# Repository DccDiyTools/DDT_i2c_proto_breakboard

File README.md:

# DDT_i2c_proto_breakboard
Breakboard of the DDT_i2c_proto specs

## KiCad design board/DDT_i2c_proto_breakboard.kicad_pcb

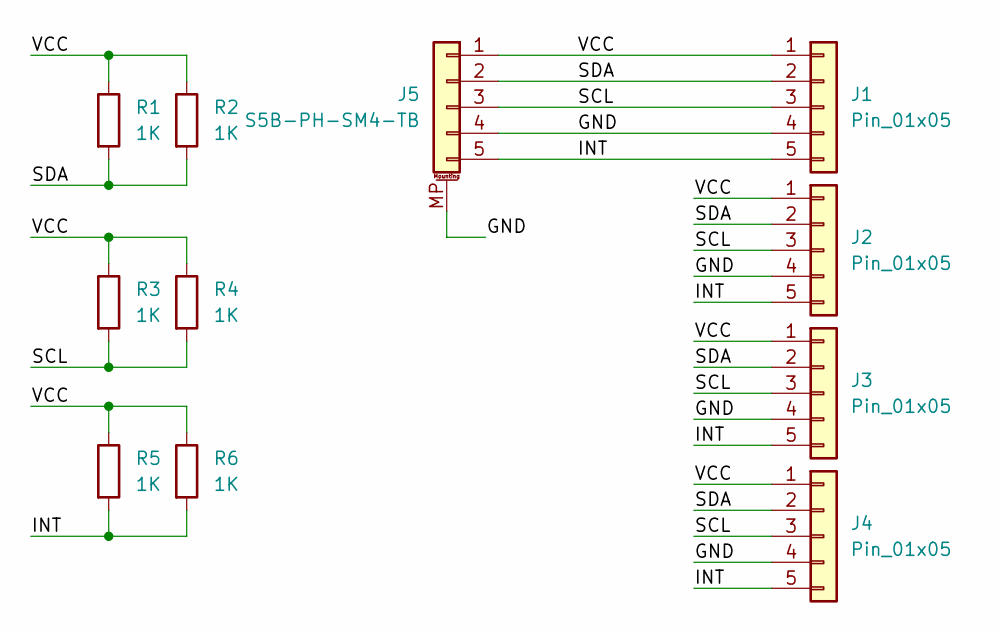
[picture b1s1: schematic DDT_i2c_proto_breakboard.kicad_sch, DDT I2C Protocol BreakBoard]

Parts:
J1, J2, J3, J4: Pin_01x05; PinHeader_1x05_P2.54mm_Vertical
J5: S5B-PH-SM4-TB; JST_PH_S5B-PH-SM4-TB_1x05-1MP_P2.00mm_Horizontal
R1, R3, R5: 1K; R_1206_3216Metric_Pad1.30x1.75mm_HandSolder
R2, R4, R6: 1K; R_Axial_DIN0309_L9.0mm_D3.2mm_P12.70mm_Horizontal

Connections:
/GND: J1.4, J2.4, J3.4, J4.4, J5.4, J5.MP (MountPin)
/INT: J1.5, J2.5, J3.5, J4.5, J5.5, R5.2, R6.2
/SCL: J1.3, J2.3, J3.3, J4.3, J5.3, R3.2, R4.2
/SDA: J1.2, J2.2, J3.2, J4.2, J5.2, R1.2, R2.2
/VCC: J1.1, J2.1, J3.1, J4.1, J5.1, R1.1, R2.1, R3.1, R4.1, R5.1, R6.1

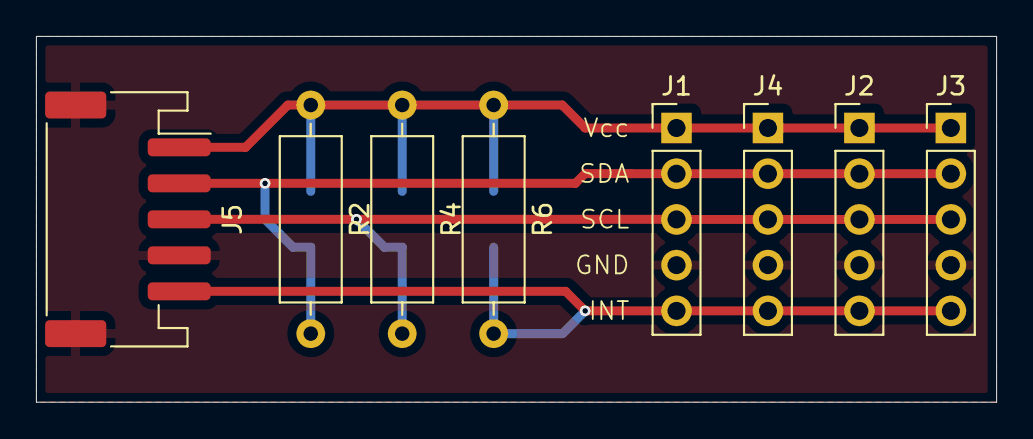
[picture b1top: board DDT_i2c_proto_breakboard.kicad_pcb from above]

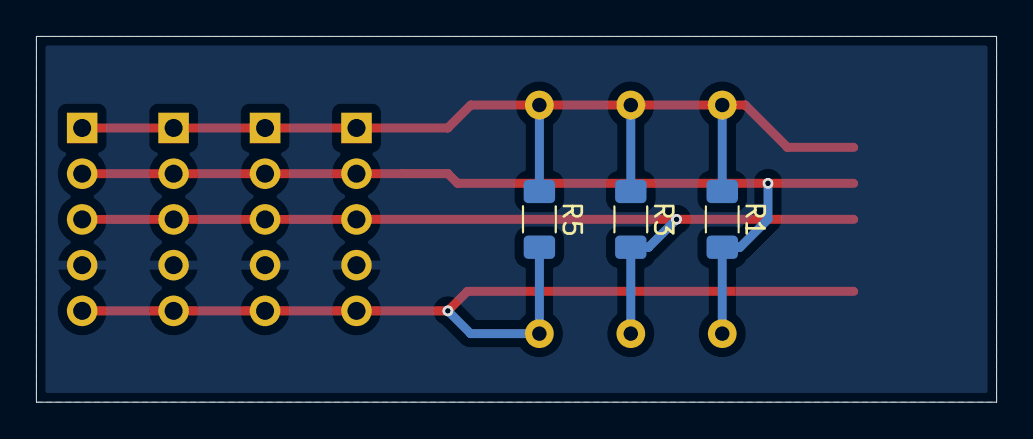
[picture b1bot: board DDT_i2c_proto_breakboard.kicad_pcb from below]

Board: 2 copper layers, 53.3 x 20.3 mm, 11 parts (3 on the bottom side), 5 nets.

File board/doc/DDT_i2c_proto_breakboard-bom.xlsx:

|  | Bill of Materials
 |  | Schematic: | DDT_i2c_proto_breakboard | Component Groups: | 4
 |  | Variant: | default | Component Count: | 11 (4 SMD/ 7 THT)
 |  | Revision: | r1 | Fitted Components: | 11 (4 SMD/ 7 THT)
 |  | Date: | 2024-08-19 | Number of PCBs: | 1
 |  | KiCad Version: | 8.0.3+1 | Total Components: | 11
Row | Description | Part | References | Value | Footprint | Quantity Per PCB | Status | Datasheet
1 | Generic connector, single row, 01x05, script generated (kicad-library-utils/sch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 | Conn_01x05 | J1 J2 J3 J4 | Pin_01x05 | PinHeader_1x05_P2.54mm_Vertical | 4 |  | ~
2 | Generic connectable mounting pin connector, single row, 01x05, script generated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 | Conn_01x05_MountingPin | J5 | S5B-PH-SM4-TB | JST_PH_S5B-PH-SM4-TB_1x05-1MP_P2.00mm_Horizontal | 1 |  | ~
3 | Resistor | R | R1 R3 R5 | 1K | R_1206_3216Metric_Pad1.30x1.75mm_HandSolder | 3 |  | ~
4 | Resistor | R | R2 R4 R6 | 1K | R_Axial_DIN0309_L9.0mm_D3.2mm_P12.70mm_Horizontal | 3 |  | ~

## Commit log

2024-08-14 First Version
2024-08-16 Update to use kibot repo
2024-08-16 Clean lck
2024-08-19 Doc tags and PCB_Way files
2024-08-19 Start of coords
